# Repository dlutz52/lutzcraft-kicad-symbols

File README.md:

# lutzcraft-kicad-symbols
Where I keep my symbols and footprints used in KiCad

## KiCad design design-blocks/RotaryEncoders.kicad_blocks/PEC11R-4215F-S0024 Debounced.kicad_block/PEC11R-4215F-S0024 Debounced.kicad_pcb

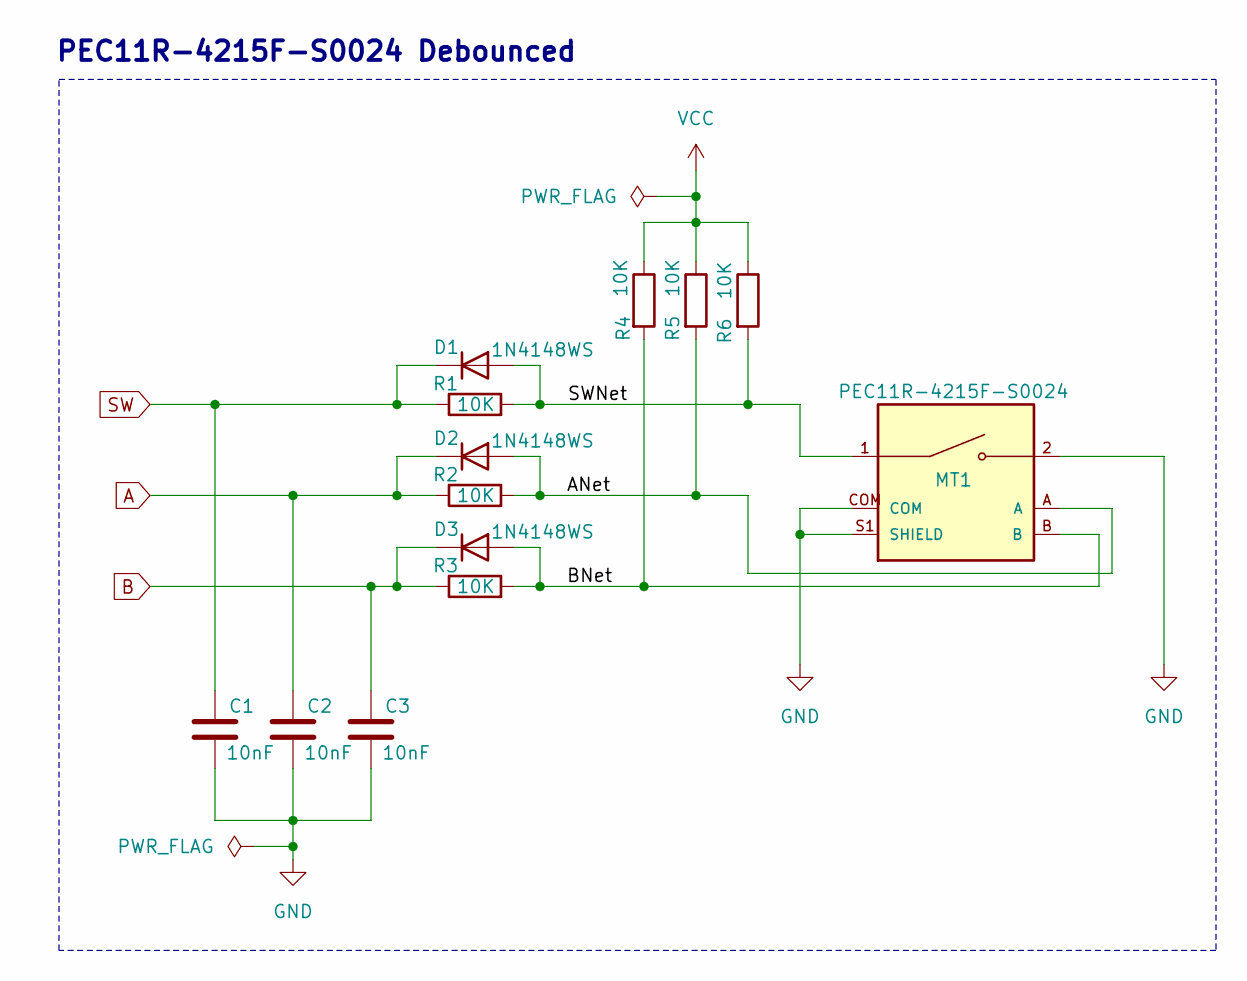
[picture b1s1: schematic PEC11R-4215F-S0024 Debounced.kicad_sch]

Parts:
C1, C2, C3: 10nF; C_0805_2012Metric_Pad1.18x1.45mm_HandSolder
D1, D2, D3: 1N4148WS; D_0805_2012Metric_Pad1.15x1.40mm_HandSolder
MT1: PEC11R-4215F-S0024; XDCR_PEC11R-4215F-S0024; PARTREV Rev. 09/19; DigikeyPN PEC11R-4015F-S0024-ND
R1, R2, R3, R4, R5, R6: 10K; R_0805_2012Metric_Pad1.20x1.40mm_HandSolder

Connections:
/ANet: D2.2 (A), MT1.A, R2.2, R5.2
/BNet: D3.2 (A), MT1.B, R3.2, R4.2
/SWNet: D1.2 (A), MT1.1, R1.2, R6.2
A: C2.1, D2.1 (K), R2.1; also elsewhere on the board
B: C3.1, D3.1 (K), R3.1; also elsewhere on the board
GND: C1.2, C2.2, C3.2, MT1.2, MT1.COM, MT1.S1 (SHIELD), MT1.S2 (SHIELD); also elsewhere on the board
SW: C1.1, D1.1 (K), R1.1; also elsewhere on the board
VCC: R4.1, R5.1, R6.1; also elsewhere on the board

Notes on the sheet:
PEC11R-4215F-S0024 Debounced

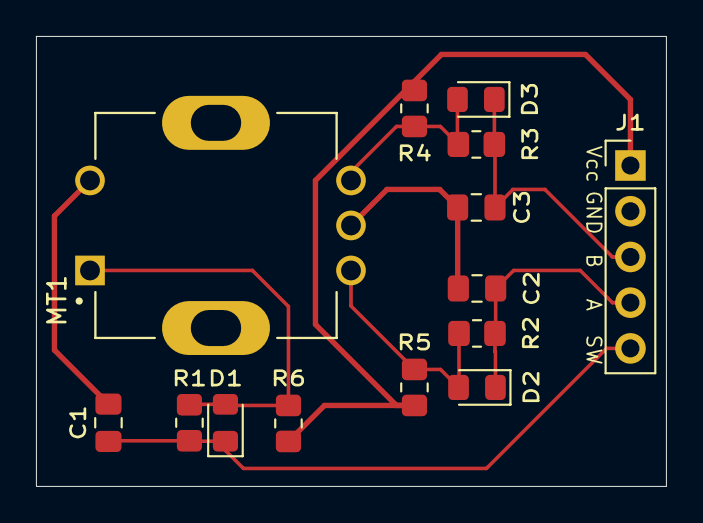
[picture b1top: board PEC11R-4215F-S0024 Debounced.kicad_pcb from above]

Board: 2 copper layers, 35.0 x 25.0 mm, 14 parts (0 on the bottom side), 8 nets.

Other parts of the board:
J1: Conn_01x05_Pin; PinHeader_1x05_P2.54mm_Vertical

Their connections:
A: J1.4; also elsewhere on the board
B: J1.3; also elsewhere on the board
GND: J1.2; also elsewhere on the board
SW: J1.5; also elsewhere on the board
VCC: J1.1; also elsewhere on the board

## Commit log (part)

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2024-09-09 Recreating this repository as the previous does not appear to exist or leat not with this account.
2024-09-09 Update README.md
    Fix typo
2024-09-09 Updated mouse-bite-1mm-slot.kicad_mod.
2024-10-07 Changes after adding SMD components for HardwareAcademy custom-esp32-pcb project.
2024-10-22 Added more symbols/footprints/3D models
2024-10-31 Added 831018077 oscillator and AT45DB081E/AT45DB161E flash chips
2025-05-11 Updating remote repo with local changes.
2025-07-09 Adding latest additions and changes.
2025-09-15 Checking in latest.
2025-10-08 Added symbol/footprint/3d-model for 3 pos dip switch. 208-3.STEP is not used.
2025-10-18 Added 'TB002-500-02BE', a three position dip switch.
2025-10-31 Replaced all instances if '${LUTZCRAFT_LIBS}/3dmodels/' in kicad_mod files with '${LUTZCRAFT_3DMODELS_DIR}/'.
2025-10-31 Add IMUs from Digikey Order #95464517.
2025-11-05 Added IST8310 IMU symbols, footprint and 3D model.
2025-12-26 Checking in recent changes.
2026-01-23 Added STM32F407ZG and corrected many path errors.
2026-01-31 Additions during D:\KiCad\projects\_dtl\stm32-dream-project\stm32h407-disco-proto project.
2026-02-02 Made several changes to ESP32 3D models.
2026-05-27 Added design-blocks and various symbols/footprints/models.
2026-05-27 Added net labels, PCB (with new pin header labels) and project folders for lib/sim and lib/fp (including lib/3d).
